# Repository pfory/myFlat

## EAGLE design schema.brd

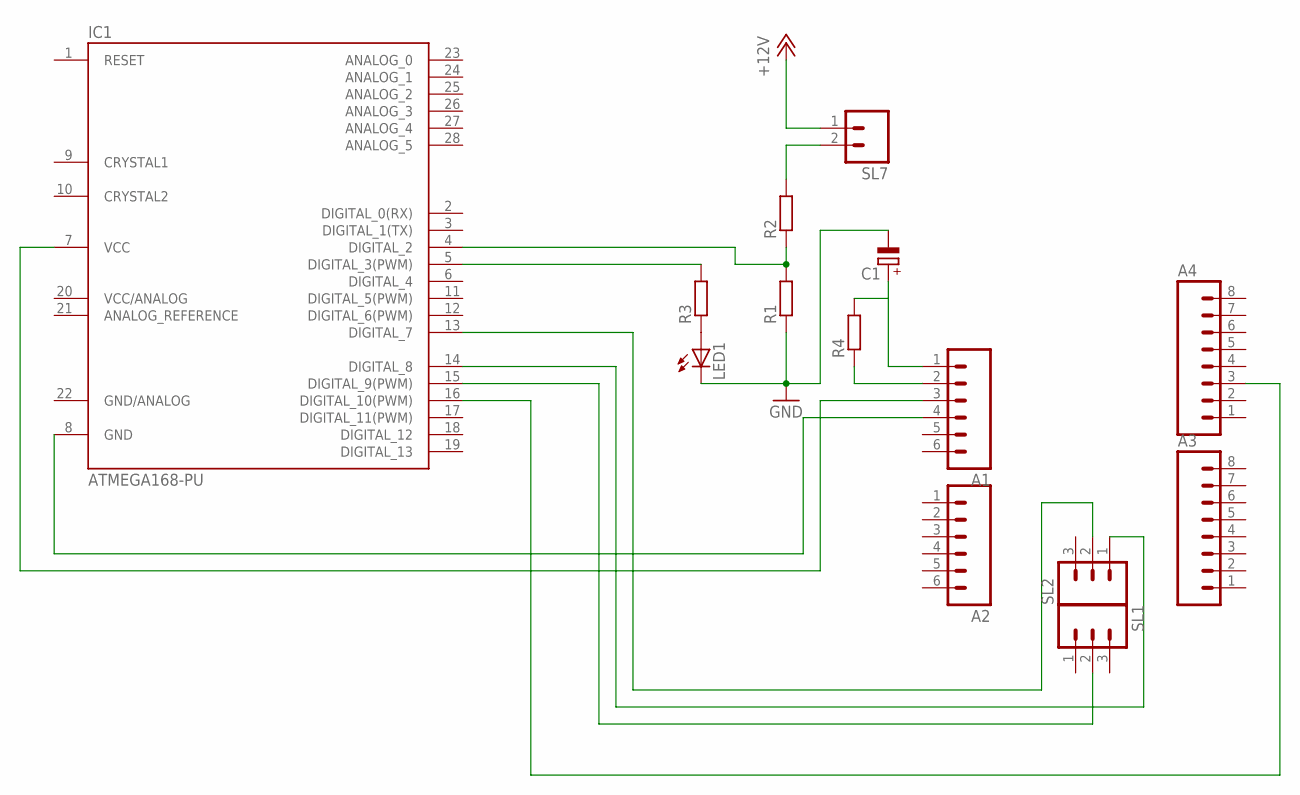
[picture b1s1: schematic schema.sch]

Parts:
A1, A2: M06; 06P
A3, A4: M08; 08P
C1: CPOL-EUE2,5-6E; E2,5-6E
IC1: ATMEGA168-PU; DIL28-3
LED1: LED3MM
R1, R2, R3, R4: R-EU_0207/7; 0207/7
SL1, SL2: M03; 03P
SL7: M02; 02P

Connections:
+12V: SL7.1
GND: C1.-, LED1.K (C), R1.1
GND/ANALOG: IC1.22 (GND/ANALOG)
unnamed: A4.3, IC1.16 (DIGITAL_10(PWM))
unnamed: IC1.15 (DIGITAL_9(PWM)), SL1.2
unnamed: IC1.14 (DIGITAL_8), SL2.1
unnamed: IC1.13 (DIGITAL_7), SL2.2
unnamed: A1.3, IC1.7 (VCC)
unnamed: A1.4, IC1.8 (GND)
unnamed: IC1.4 (DIGITAL_2), R1.2, R2.1
unnamed: A1.1, C1.+, R4.2
unnamed: R2.2, SL7.2
unnamed: LED1.A, R3.1
unnamed: IC1.5 (DIGITAL_3(PWM)), R3.2
unnamed: A1.2, R4.1

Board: 2 copper layers, 14 parts (0 on the bottom side), 13 nets, no tracks yet.

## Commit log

2015-04-22 :octocat: Added .gitattributes & .gitignore files
2015-04-22 EDITED
2015-04-27 rename
2015-04-27 nacitani stavu pri startu
2015-04-28 +hodinove a denni spotreby
2015-04-28 zaloha
2015-04-28 Merge remote-tracking branch 'origin/master'
    Conflicts:
    myFlat.ino
2015-04-28 verze
2015-04-28 knihovna
2015-04-28 v0,2
2015-04-29 +sledovani prikonu
2015-04-29 graficke zmeny
2015-04-30 v0.3
2015-04-30 zmena verze
2015-05-03 +display
2015-05-20 v0,23
2015-05-20 v0,24
2015-05-21 0.25
2015-05-22 + comments
2015-05-28 +schema eagle
2015-11-11 rename myFlatESP8266.ino
2015-12-09 +vypocet prikonu
2016-02-18 pred predelavkou na openHAB
2016-03-03 +eeprom
